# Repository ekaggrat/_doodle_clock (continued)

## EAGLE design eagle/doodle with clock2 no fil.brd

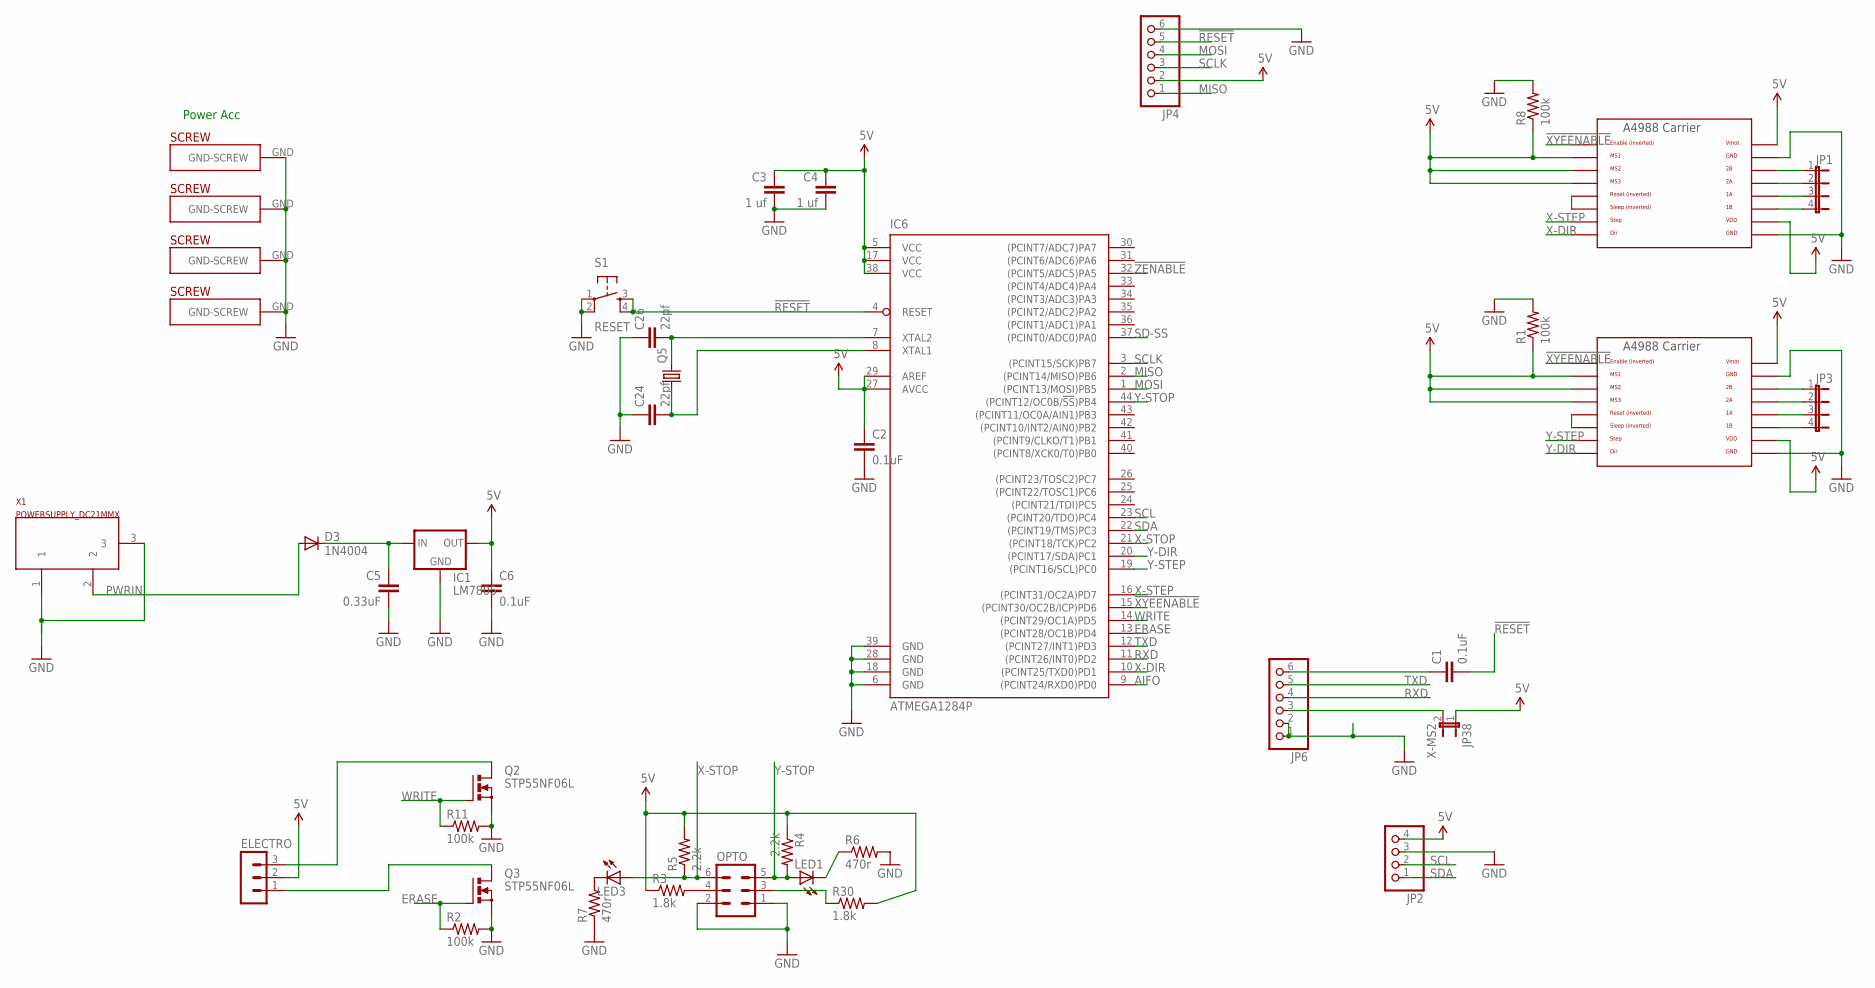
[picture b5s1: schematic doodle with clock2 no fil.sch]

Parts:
C1, C2, C6: 0.1uF; CAP-PTH-SMALL2
C3, C4: 1 uf; CAP-PTH-SMALL2
C5: 0.33uF; CAP-PTH-SMALL2
C24, C26: 22pf; CAP-PTH-SMALL2
D3: 1N4004; DO41-10
ELECTRO: MA03-1
IC1: LM7805; 78XXL-CUSTOM
IC6: ATMEGA1284P; TQFP44
JP1, JP3: JP4E; JP4
JP2: PINHD-1X4; 1X04
JP4: PINHD-1X6/90; 1X06/90
JP6: PINHD-1X6; 1X06
JP38: X-MS2; 1X02
LED1, LED3: LED3MM
OPTO: MA03-2
Q2, Q3: STP55NF06L; TO220BV
Q5: CRYSTALHC49S; HC49/S
R1, R8: 100k; 0207/7
R2, R11: 100k; 0207/2V
R3, R30: 1.8k; 0207/2V
R4, R5: 2.2k; 0207/2V
R6, R7: 470r; 0207/2V
S1: RESET; TACTILE-PTH
U$1, U$7: A4988BREAKOUT
U$14, U$17, U$18, U$38: PLATED-SCREW; PLATEDSCREW
X1: POWERSUPPLY_DC21MMX; POWERSUPPLY_DC-21MM

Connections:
5V: C2.1, C3.1, C4.1, C6.1, ELECTRO.2, IC1.OUT, IC6.5 (VCC), IC6.17 (VCC), IC6.27 (AVCC), IC6.29 (AREF), IC6.38 (VCC), JP2.4, JP4.2, JP38.1, R1.1, R3.1, R4.1, R5.2, R8.1, R30.2, U$1.MS1, U$1.MS2, U$1.MS3, U$1.VDD, U$1.VMOT, U$7.MS1, U$7.MS2, U$7.MS3, U$7.VDD, U$7.VMOT
!RESET: C1.2, IC6.4 (RESET), JP4.5, S1.3, S1.4
!XYEENABLE: IC6.15 ((PCINT30/OC2B/ICP)PD6), U$1.EN, U$7.EN
!ZENABLE: IC6.32 ((PCINT5/ADC5)PA5)
AIFO: IC6.9 ((PCINT24/RXD0)PD0)
ERASE: IC6.13 ((PCINT28/OC1B)PD4), Q3.G, R2.1
GND: C2.2, C3.2, C4.2, C5.2, C6.2, C24.1, C26.1, IC1.GND, IC6.6 (GND), IC6.18 (GND), IC6.28 (GND), IC6.39 (GND), JP2.3, JP4.6, JP6.1, JP6.2, OPTO.1, OPTO.2, Q2.S, Q3.S, R1.2, R2.2, R6.2, R7.1, R8.2, R11.2, S1.1, S1.2, U$1.GND, U$1.GND@0 (GND), U$7.GND, U$7.GND@0 (GND), U$14.GND, U$17.GND, U$18.GND, U$38.GND, X1.1, X1.3
MISO: IC6.2 ((PCINT14/MISO)PB6), JP4.1
MOSI: IC6.1 ((PCINT13/MOSI)PB5), JP4.4
unnamed: U$1.RST, U$1.SLP (SLEEP)
unnamed: JP3.1, U$1.2B
unnamed: JP3.2, U$1.2A
unnamed: JP3.3, U$1.1A
unnamed: JP3.4, U$1.1B
unnamed: ELECTRO.1, Q3.D
unnamed: OPTO.4, R3.2
unnamed: ELECTRO.3, Q2.D
unnamed: LED1.K (C), R6.1
unnamed: LED3.K (C), R7.2
unnamed: OPTO.3, R30.1
unnamed: JP1.1, U$7.2B
unnamed: JP1.2, U$7.2A
unnamed: JP1.3, U$7.1A
unnamed: JP1.4, U$7.1B
unnamed: U$7.RST, U$7.SLP (SLEEP)
unnamed: C5.1, D3.C, IC1.IN
unnamed: C1.1, JP6.6
unnamed: JP6.3, JP38.2
unnamed: C26.2, IC6.7 (XTAL2), Q5.2
unnamed: C24.2, IC6.8 (XTAL1), Q5.1
PWRIN: D3.A, X1.2
RXD: IC6.11 ((PCINT26/INT0)PD2), JP6.4
SCL: IC6.23 ((PCINT20/TDO)PC4), JP2.2
SCLK: IC6.3 ((PCINT15/SCK)PB7), JP4.3
SD-SS: IC6.37 ((PCINT0/ADC0)PA0)
SDA: IC6.22 ((PCINT19/TMS)PC3), JP2.1
TXD: IC6.12 ((PCINT27/INT1)PD3), JP6.5
WRITE: IC6.14 ((PCINT29/OC1A)PD5), Q2.G, R11.1
X-DIR: IC6.10 ((PCINT25/TXD0)PD1), U$7.DIR
X-STEP: IC6.16 ((PCINT31/OC2A)PD7), U$7.STEP
X-STOP: IC6.21 ((PCINT18/TCK)PC2), LED3.A, OPTO.6, R5.1
Y-DIR: IC6.20 ((PCINT17/SDA)PC1), U$1.DIR
Y-STEP: IC6.19 ((PCINT16/SCL)PC0), U$1.STEP
Y-STOP: IC6.44 ((PCINT12/OC0B/!SS!)PB4), LED1.A, OPTO.5, R4.2

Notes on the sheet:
Power Acc

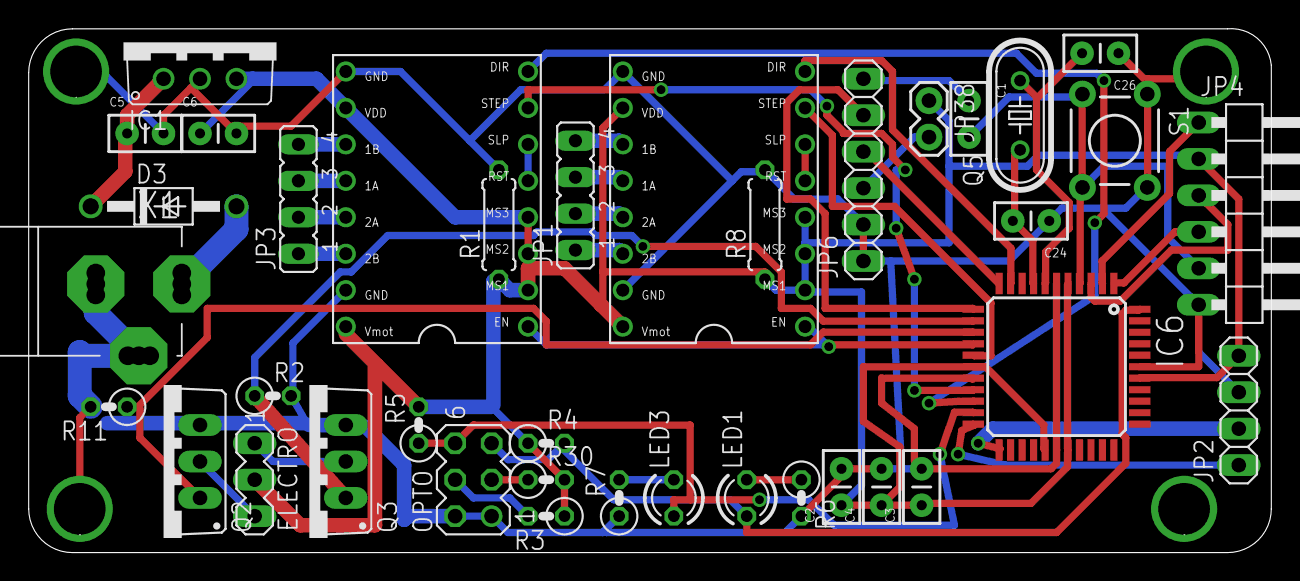
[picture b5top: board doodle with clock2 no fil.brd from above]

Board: 2 copper layers, 86.6 x 36.5 mm, 42 parts (0 on the bottom side), 41 nets.

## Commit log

2013-11-25 new pcb
2013-11-25 pcb 4
2013-12-04 pcb version 3
2013-12-04 328 and rtc narrow
2013-12-06 on board clock added
2013-12-12 acrylic and pcb update
2013-12-18 new plastic model
2013-12-19 new plastic simulation
2013-12-19 parallel scara arm
2013-12-20 l293dd board with on board clock
2013-12-22 encoder script
2013-12-23 scara arm gh
2013-12-23 scara arm finally works
2013-12-24 gearless scara
2013-12-26 gear less scara for print
2013-12-26 crap
2013-12-26 gearless scara for prusa with old arm
2014-01-01 digit test
2014-01-13 screw arm try
2014-01-14 vertical screw thread
2014-01-26 screw drive motor
